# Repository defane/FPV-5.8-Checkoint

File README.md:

# Lëtz Timer

*(technical name: `LetzTimer`; formerly "FPV 5.8 Checkpoint")*

A **"a drone just passed"** platform: a C5 sweeps the 8 Raceband channels and
detects a drone pass on any of them, and a C6 master times it and plays a coin sound, with a
phone-friendly web UI to tune it and watch events. Each gate is a C5 wired to a
C3 (or to the C6); a C3 with no master in reach serves its own web page with the
passes. It scales to a multi-gate race-timing fleet.

> **Derivative and credits.** The detector's receive engine (`components/sdr_rx`) is ported from
> [widscan58](https://github.com/CapnBry/widscan58) by **CapnBry** (commit `a9fff97`: radio, calibration
> cache, PSD/FFT, level metrics, LO planner, linker guard), whose radio layer is derived from
> [esp-sdr](https://github.com/ESPARGOS/esp-sdr) by **ESPARGOS** (commit `a8eaac1`: the PHY I/Q dump
> capture, RX path, gain and analog filter control). Those files keep their GPL-3.0-or-later notices.
> This project started from [C5VRX](https://github.com/Twotoz/C5VRX) — **C5VRX-5, by Twotoz and the C5VRX
> contributors** (upstream `6bc9e4b`) — and is no longer a fork: the C5VRX receive engine was removed (issue #2) and
> the platform around it is new. Some C5VRX material remains and keeps its credit: the C5 PHY I/Q dump format first decoded by C5VRX-1, the console
> structure, the firmware id and NVS helpers, the Raceband scan benches and the off-grid tuning finding
> (zerowidth PR #3). Visit the [official C5VRX website](https://twotoz.github.io/C5VRX/) for the original
> project; its Discord invite is available there. This repository adds the pass detector, the coin
> sound (on the C6 master), and the C5↔C3/C6 platform around it. GPL-3.0-only (see `LICENSE`), without
> any warranty (sections 15–17); the C3 and C6 web pages show this notice in their footer. Not an
> official release of C5VRX, esp-sdr or widscan58, and not endorsed by their authors.

## What it is

- **ESP32-C5** (`firmware/detector`, Waveshare ESP32-C5-Zero) — runs the **sdr_rx**
  engine (`components/sdr_rx`): snapshots of the PHY's I/Q dump at 80 MS/s, one LO for
  two channels (5677/5751/5825/5899 MHz), a 4 × 64-point integer PSD with moment-based
  I/Q correction and the ±5 MHz band power of each channel, ~500 times a second per
  channel (widscan58's measurement; not yet measured on this board). It detects a pass
  on any of R1 to R8 and reports it over a UART link to its bridge. It has no local
  output: no picture, no amplifier and no status LED.
- **ESP32-C3** (`firmware/node`) — a node bridge: UART to the C5, ESP-NOW uplink to
  the C6 master; if no master is reachable at boot it falls back to a local
  Wi-Fi SoftAP + web (results, the C5's health and its
  calibrate/reboot commands).
- **ESP32-C6** (`firmware/master`) — the optional **race-timing master**: UART to its
  own C5, the centralized speaker, a Wi-Fi AP web, and an ESP-NOW hub that
  aggregates the C3 nodes. Each gate is a C5; the C6 times laps per channel,
  shows every gate's health and runs its calibrations and reboots (production
  has no USB console: [docs/fleet.md](docs/fleet.md#gate-health-and-remote-commands-no-console-in-production)).

The web has **two roles**: **spectators** watch the live standings and status
read-only (no login), while **admin** actions — pairing, gate order, reset,
volume, the fleet's re-arm drop, a gate's calibration or reboot, and (on a
degraded C3) detector tuning — require the admin password
(`CONFIG_*_ADMIN_PASSWORD`, no username): the admin toggle in the
header opens a password dialog. The password never crosses the Wi-Fi: the page
signs each admin request (HMAC-SHA256, per-session counter against replays)
with a key derived from it (PBKDF2), the only form the firmware holds (the tab keeps that key, never
the password, in its sessionStorage, so a reload stays admin until the tab closes or you switch admin off). A sniffed
request still allows offline guessing, so choose a long random password
([docs/fleet.md](docs/fleet.md), `components/web_auth`).

## Layout

```
components/
  sdr_rx/        receive engine (C5 only): dump capture, LO pairs, PSD + IQ correction (pure-C parts host-tested)
  letztimer/     the scan task, console and benches, pass detection + the C5<->bridge UART link
  pass_detector/ pure-C pass detector and scan detector (host-tested)
  audio_player/  I2S coin-sound player (the C6 speaker in a fleet)
  link_proto/    pure-C C5<->bridge UART protocol (host-tested)
  fleet_proto/   pure-C C6<->C3 ESP-NOW protocol (host-tested)
  race_timing/   pure-C lap/sector timing engine (host-tested)
  espnow_link/   ESP-NOW transport carrying fleet_proto (C6 + C3)
  status_led/    single-WS2812 status indicator (pure-C core host-tested)
  web_auth/      signed admin requests for the C3/C6 web (pure-C core + auth.js host-tested)
firmware/detector/  ESP32-C5 application (RF + detection, report-only)
firmware/node/      ESP32-C3 node bridge (UART + ESP-NOW relay, degraded Wi-Fi web)
firmware/master/    ESP32-C6 master (UART + ESP-NOW hub + speaker + admin web + timing)
docs/            LETZTIMER.md (index) + detector/no-video-audio/fleet/status-led/bench, wiring-*.svg
```

See **[docs/LETZTIMER.md](docs/LETZTIMER.md)** for the feature notes, the fleet
and the bench procedure, and **[docs/wiring-node.svg](docs/wiring-node.svg)** for
a gate's wiring (C3 + C5).

## Build

The root `Makefile` is the quick path: `make firmware` builds every variant,
`make flash [FW=<name>] [PORT=<port>]` flashes one (interactive firmware/port
menu if an arg is omitted), `make monitor`, `make variants` (list the `FW=`
names: `detector`/`node`/`master` defaults plus variants like
`detector-ipex` (a C5-Zero on its IPEX connector, for an external antenna),
`detector-xiao-c5`, `detector-wave-c5-lcd`, `master-wave-c5`, `master-wave-s3`), `make clean`. flash/monitor fall
back to esptool / a serial terminal on the already-built image when ESP-IDF is
not installed, so you can build in one place and flash in another.

For local, uncommitted settings — the Wi-Fi AP and admin-web passwords, or
enabling audio — put them in `firmware/<role>/sdkconfig.local.defaults` (one
`CONFIG_...=...` per line). It is gitignored, and `make`/`tools/fw.sh` append it
last so it overrides the committed defaults.

To work on the web pages without a board, `make web-master` (<http://127.0.0.1:8080/>)
or `make web-node` (port 8081) runs `tools/web_mock.py`: it serves the real pages from
disk, so a browser reload shows an edit, no build and no flash. `/api/*` answers like
the firmware on a simulated race (now and then a drone lingers at a gate, its channel
framed in cooldown), admin actions take effect (password `letztimer`) and
signed requests are checked as on the ESP. `WEB_ARGS` passes its options: `--vtx` (a
strong carrier on every gate, for the calibration guard; each gate's channel then stays
in cooldown after its first pass), `--latency 300`, `--host
0.0.0.0` (to open it from a phone), `--password ""`. Stopping and restarting it is an
ESP reboot.

The raw commands:

```sh
. ~/esp/esp-idf-v6.0.2/export.sh
( cd firmware/detector && idf.py build )  # esp32c5 → build/detector-c5.bin (0 warnings)
( cd firmware/node && idf.py build )      # esp32c3 → build/node-c3.bin
( cd firmware/master && idf.py build )    # esp32c6 → build/master-c6.bin
# temporary "C5 as master" (run the master firmware on a spare C5 until the C6 arrives) → build-c5/master-c5.bin:
( cd firmware/master && idf.py -DIDF_TARGET=esp32c5 -DSDKCONFIG=sdkconfig.c5 \
    -DSDKCONFIG_DEFAULTS=sdkconfig.c5.defaults -B build-c5 build )

# Host tests
cd test
cc -O2 -std=c11 -Wall -Wextra -Werror -I../components/sdr_rx -I../components/sdr_rx/include test_sdr_dsp.c \
   ../components/sdr_rx/sdr_psd.c ../components/sdr_rx/sdr_level.c -lm -o /tmp/t && /tmp/t
cc -O2 -std=c11 -Wall -Wextra -Werror -I../components/sdr_rx -I../components/sdr_rx/include test_sdr_plan.c \
   ../components/sdr_rx/sdr_plan.c -o /tmp/t && /tmp/t
cc -O2 -std=c11 -Wall -Wextra -Werror -I../components/pass_detector/include \
   test_pass_detector.c ../components/pass_detector/pass_detector.c -lm -o /tmp/t && /tmp/t
cc -O2 -std=c11 -Wall -Wextra -Werror -I../components/pass_detector/include test_scan_detector.c \
   ../components/pass_detector/scan_detector.c ../components/pass_detector/pass_detector.c -lm -o /tmp/t && /tmp/t
cc -O2 -std=c11 -Wall -Wextra -Werror -I../components/pass_detector/include -I../components/sdr_rx \
   -I../components/sdr_rx/include test_pair_ghost.c ../components/pass_detector/scan_detector.c \
   ../components/pass_detector/pass_detector.c ../components/sdr_rx/sdr_psd.c ../components/sdr_rx/sdr_level.c \
   ../components/sdr_rx/sdr_plan.c -lm -o /tmp/t && /tmp/t   # the guard end to end on the DSP
cc -O2 -std=c11 -Wall -Wextra -Werror -I../components/audio_player/include \
   test_audio_resample.c -lm -o /tmp/t && /tmp/t
cc -O2 -std=c11 -Wall -Wextra -Werror -I../components/link_proto/include \
   test_link_proto.c ../components/link_proto/link_proto.c -o /tmp/t && /tmp/t
cc -O2 -std=c11 -Wall -Wextra -Werror -I../components/fleet_proto/include -I../components/link_proto/include \
   test_fleet_proto.c ../components/fleet_proto/fleet_proto.c ../components/link_proto/link_proto.c -o /tmp/t && /tmp/t
cc -O2 -std=c11 -Wall -Wextra -Werror -I../components/race_timing/include \
   test_race_timing.c ../components/race_timing/race_timing.c -o /tmp/t && /tmp/t
cc -O2 -std=c11 -Wall -Wextra -Werror -I../components/status_led/include \
   test_status_led.c ../components/status_led/status_led.c -o /tmp/t && /tmp/t
cc -O2 -std=c11 -Wall -Wextra -Werror -I../components/web_auth/include \
   test_web_auth.c ../components/web_auth/web_auth.c -o /tmp/t && /tmp/t
cc -O2 -std=c11 -Wall -Wextra -Werror -I../components/letztimer \
   test_hop_stats.c -lm -o /tmp/t && /tmp/t
node test_web_auth.mjs   # the page side (auth.js), Node 18+
node test_web_bubble.mjs # the pages' info bubbles: one snippet, mouse, touch and keyboard
python3 test_web_mock.py # tools/web_mock.py against the firmware's /api/state and buffers
python3 test_pcb.py      # hardware/ boards against the firmware's Kconfig pin defaults
python3 test_scan_analyze.py   # tools/scan_analyze.py on synthetic recordings
python3 test_flash_tool.py     # tools/flash.py: download key, --check, logs
```

After editing a `firmware/detector/sdkconfig*.defaults`, run `tools/fw.sh clean`: it
deletes every build dir and generated `sdkconfig`/`sdkconfig.<variant>` (never a
`*.defaults`), since ESP-IDF never reapplies the defaults.

## Architecture

- **Global schema:** at the top of this page ([docs/fleet.svg](docs/fleet.svg)).
- **Pin-level wiring, per set type:**
  - master **C6 + C5**: [docs/wiring-master.svg](docs/wiring-master.svg)
  - node **C3 + C5** (also a gate with no master: the C3 then serves the web): [docs/wiring-node.svg](docs/wiring-node.svg)
  - temporary **C5 + C5** (a spare C5 runs the master firmware until the C6 arrives): [docs/wiring-c5c5.svg](docs/wiring-c5c5.svg)

## Pinout

Each UART link is crossed (one side's TX to the other's RX) with a common
ground. Pins are Kconfig defaults (`menuconfig`). USB-Serial-JTAG (flashing/console)
is reserved on every board. [`hardware/`](hardware/README.md) has carrier PCBs for
both sets, with Gerbers ready to order.

**ESP32-C5** (`firmware/detector`, detector — one per gate)

| Function | GPIO | Notes |
| --- | --- | --- |
| Link UART TX → bridge RX | 6 | to a C3 (node) or the C6 (master) |
| Link UART RX ← bridge TX | 8 | C5-Zero header pin (GPIO 15 is not broken out) |
| Amplifier / status LED | — | none on a detector: the C6 master plays the sound |
| forbidden | 13,14 (USB) · 16-22 (flash) · 26 (antenna) | console, flash, C5-Zero antenna switch |
| free | 0-5, 7, 9-12, 23-25, 27 | the sdr_rx engine uses no GPIO; 2, 7, 25, 27 (and 28, BOOT) are strapping pins: free after boot, no external pull or load that holds them at reset; 27 is the C5-Zero's WS2812 (unused) |

**ESP32-C3** (`firmware/node`, node bridge)

| Function | GPIO | Notes |
| --- | --- | --- |
| UART TX → C5 RX (8) | 5 | |
| UART RX ← C5 TX (6) | 4 | |
| Wi-Fi / ESP-NOW | — | no GPIO; ESP-NOW to the C6 on the shared AP channel |

**ESP32-C6** (`firmware/master`, master)

| Function | GPIO | Notes |
| --- | --- | --- |
| UART TX → local C5 RX (8) | 4 | |
| UART RX ← local C5 TX (6) | 5 | |
| Amplifier BCLK / LRC / DIN / SD | 18 / 19 / 20 / 21 | the centralized speaker; `VIN` 5 V, `OUT±` to a 4 Ω speaker |
| Wi-Fi AP + ESP-NOW | — | admin web + fleet hub; same channel as the nodes |

The C6 AP, the C3 APs and ESP-NOW must share the **same Wi-Fi channel**
(`CONFIG_C6_AP_CHANNEL` / `CONFIG_C3_AP_CHANNEL`).

## Safety

> [!WARNING]
> This is experimental and built on an experimental receive engine. Bugs, signal
> loss or automatic receive-chain changes can cause missed or false passes even
> after an apparently successful test. Do not rely on it as your only means of
> maintaining safe control of an aircraft.

## Attribution

Receive engine (`components/sdr_rx`): **widscan58** by CapnBry —
<https://github.com/CapnBry/widscan58>, commit `a9fff97`. Ported from its
`firmware/src/radio/` (`radio.h`; `c5/radio_c5.c`, `recal_c5.c`, `sram_guard.ld`,
`hot_iram.lf`), `firmware/src/dsp/` (`psd.c`, `fft_r4_sc16.h`, `fft_twiddle_q15.h`) and
`firmware/src/scan/` (`metrics.c`, `planner.c`, the hop of `scanner.c`); the bench
methods of `components/letztimer/lt_bench.c` (tune timing, settle, image rejection,
noise per FFT size) follow its measurement log (`PLAN.md`). Its radio layer is derived
from **esp-sdr** by ESPARGOS — <https://github.com/ESPARGOS/esp-sdr>, commit `a8eaac1`
(`main/families/c5_c6_c61/receiver.c`, `main/targets/esp32c5/`,
`main/common/rx_recalibration.c`, `main/common/burst_gain.h`). The ported files keep
their GPL-3.0-or-later notices and list their changes in their headers.

History: this project started from **C5VRX** by Twotoz and the C5VRX contributors, and is no longer a fork —
<https://github.com/Twotoz/C5VRX> · <https://twotoz.github.io/C5VRX/> (Discord
invite on the website), at upstream `6bc9e4b`. The C5VRX-5 receive engine ran the
detector until issue #2 and is removed (`main` keeps it until a board
bench validates sdr_rx). Still used from C5VRX-5: the console structure and its
download-key reboot (`components/letztimer/lt_console.c`, the reboot of
`components/sdr_rx/sdr_radio_c5.c`), the firmware id and NVS helpers
(`components/letztimer/fw_id.c`, `lt_nvs.c`), `tools/flash.py` and
`tools/enter_download.py`, and the off-grid tuning finding of zerowidth/C5VRX PR #3.
The Raceband scan benches first built on the C5VRX engine (issue #1) give
`lt_bench.c` the shape of its scan recording and residue trace. Reused material keeps
its original copyright, license and credits; see `AGENTS.md` for the reuse policy and
`assets/BRANDING.md` for branding terms.

Research provenance: the PHY I/Q dump engine was first decoded in C5VRX-1 (librftest
`adctrig`, registers `0x600a9004/08/18`, bank `0x40830000`, 10-bit I/Q words: upstream
`legacy/c5vrx1/research/adc-dump-format.md`), and C5VRX-3/5 drove it continuously
(`enable_continuous_modem`, upstream `main/rf.c:119-147`). sdr_rx takes a different
route: one-shot snapshots, as esp-sdr and widscan58 trigger them. Source: raw source 15,
after the PHY's ADC-rate/RX-filter stage. Rate: 80 MS/s. Size: 256 words per capture
(3.2 µs). Ownership: CPU-polled, no DMA, no ring, no DAC. Word format: I bits 0–9,
Q bits 10–19, signed.

For the history, C5VRX-5 builds on C5VRX-2..4 (the continuous MODEM_DIAG to
BitScrambler video path, Direct Gain V3-V5, the PAIR schedule and the U85Q study of
PR #190), on zerowidth/C5VRX PR #3 (interference-burst gate, sampling-phase probe,
off-grid channel tuning), on Louis Hitchcock's staged overload recovery (C5VRX
#182/#184), and on ESPARGOS esp-sdr (GPL-3.0) for the C5 RX filter control. Espressif
supplied the GDMA EOF fix (espressif/esp-idf#19091).

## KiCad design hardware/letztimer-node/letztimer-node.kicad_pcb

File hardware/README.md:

# Carrier boards

Two 2-layer boards that hold the modules of a set, every USB-C on the same edge, with solder
pads for the power.

| Board | Modules | Size | To order |
| --- | --- | --- | --- |
| node | C5-Zero + C3-Zero | 57 × 24 mm | [`gerbers/letztimer-node-gerbers.zip`](gerbers/letztimer-node-gerbers.zip) |
| master | C5-Zero + C6-Zero + MAX98357A | 79 × 24 mm | [`gerbers/letztimer-master-gerbers.zip`](gerbers/letztimer-master-gerbers.zip) |

**No board has been built yet.** The design rules pass, the drill data matches Waveshare's
drawings and `test/test_pcb.py` ties the nets to the firmware, but nothing has been soldered
or powered. Order a small batch first.

## Before ordering

Print `letztimer-*/letztimer-*-1to1.pdf` at 100 % and lay the real modules on the paper.
Check the MAX98357A closely: the footprint comes from Adafruit's board. Other breakouts
usually share its 7-pin order, but compare yours with the `LRC`…`VIN` labels on the board.

## Ordering

Upload the zip as it is. It holds both copper layers, solder mask, silkscreen, the outline
and the drill files.

2 layers, FR-4, 1.6 mm, 1 oz copper, any finish. No stencil or assembly needed.

## Parts

[`BOM.csv`](BOM.csv) lists each board's parts with an order reference. `test/test_pcb.py` checks
it against the node and master boards.

The `-M` Waveshare modules cost a little more but come with their headers fitted, which saves
the 1×9 headers and 18 joints per module. SS34 diodes must be in the **SMA** package.

## Assembly

1. Solder R1, R2, D1 and D2. The bar on a diode faces the module.
2. Before fitting a module, check J1 and J2 are not shorted, feed 5 V and read a little under
   5 V on the `5V` holes of U1 and U2.
3. Fit the modules on their headers, components up, **USB towards the top edge**. U1 hangs
   4 mm past the bottom edge, on purpose.
4. Master: fit the amplifier components up, its pin row on the `U3` labels. The speaker goes
   to the breakout's own terminal.

Then flash as usual, with `make flash FW=detector` for U1 and `FW=node` or `FW=master` for U2.

## Power

Feed the pads with **4.6 to 5.5 V**: 1 A for a node, 2 A for a master.

The `5V` pin of the C5-Zero and C3-Zero **is** the USB VBUS, with no diode (the C6-Zero has
its own B5819WS). Wired directly, a supply on the pads would feed the PC's USB port and two
cables would tie two hosts together. So each side gets its own diode, and USB can stay
plugged in while the pads are powered, which is the normal way to debug a running gate:

| Plugged in | C5 | C3 / C6 | Amplifier |
| --- | --- | --- | --- |
| Pads | on | on | on |
| USB on the C5 | on | off | off |
| USB on the C3 | off | on | — |
| USB on the C6 | off | on | on |
| Pads and any USB | on | on | on |

The diodes also protect the whole board if the power wires are swapped. They drop about 0.4 V,
which every regulator here tolerates. The 5.5 V limit is that of the C5-Zero's converter and
of the amplifier, kept on the pads as a margin.

R1 and R2 exist because of those diodes: a module can now be running while the other one is
off, and they hold the current into the sleeping chip's pin to about 3 mA. At 115200 baud
they change nothing.

## Layout notes

- **USB:** each module's end is flush with the top edge, so its USB-C sticks out by about
  1.6 mm and two plugs fit side by side. BOOT and RESET stay reachable on top.
- **Antennas:** the board stops short of the C5's ceramic antenna and IPEX connector, and a
  12 mm notch leaves no copper or FR-4 under any antenna.
- **Receiver pins:** the C5's GPIO 0 to 5 stay unconnected (they carried C5VRX's IQ
  loopback; the sdr_rx engine uses no GPIO), like every C5 pin but `5V`, `GND` and the link
  (GPIO 6 and 8). Those two are not strapping pins.
- **C6 strapping pins:** the link uses GPIO 4 and 5, which only set the SDIO clock edges and do
  not affect a boot from flash. GPIO 8, 9 and 15 are left unconnected.
- **Speaker terminal:** its pins may poke through the breakout, so the master has no copper
  under them.

## Still to check on a real board

- **Detection:** the C5's antenna now sits about 2 cm from the C3's or C6's 2.4 GHz antenna.
  Compare the `levels` and false passes with the wired setup, with Wi-Fi active.
- **Heat** in D2 on a master at full volume.
- **Temporary C5-as-master set:** not supported, its amplifier pins differ.

## Antenna

[`antenna/`](antenna/README.md) holds a directive 5.8 GHz quasi-Yagi on FR-4, a separate board
that reaches a C5-Zero through its IPEX connector. Its openEMS model gives about 4.5 dBi along its
axis across the Raceband, in a beam 64° by 84° wide. It has not been built.

## Enclosure

[`enclosure/`](enclosure/README.md) holds a 3D-printed box for a node or a master set, with its
LiPo cut-off and DC-DC converter (and the master's speaker), and an arm that points the antenna
in 8 directions and rolls it about its own axis in 8 steps. Its source is a SolidCraft design
with one configuration per set. It has not been printed yet.

## Regenerating

[`generate_boards.py`](generate_boards.py) is the source of the boards: edit it, not the KiCad
files, which it overwrites. It needs KiCad 9 (`pcbnew` and `kicad-cli`):

```sh
python3 hardware/generate_boards.py   # writes the boards, fills, runs the DRC, exports
python3 test/test_pcb.py              # no KiCad needed; run in CI
```

The DRC result is printed for each board and must read `violations [] unconnected 0`.

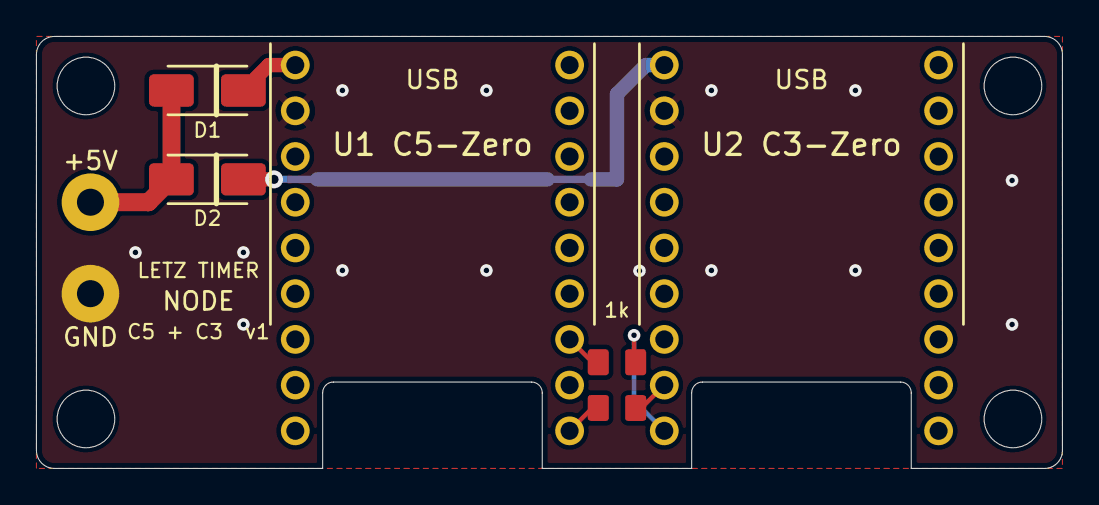
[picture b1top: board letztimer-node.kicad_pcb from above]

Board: 2 copper layers, 57.0 x 24.0 mm, 12 parts (0 on the bottom side), 8 nets.

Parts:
D1, D2: SS34 3A 40V SMA; SS34
H1, H2, H3, H4: M3 hole; M3
J1: +5V wire pad; +5V
J2: GND wire pad; GND
R1, R2: 1k 0805; 1k
U1: C5-Zero
U2: C3-Zero

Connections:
5V_BRIDGE: D2.1, U2.5V
5V_C5: D1.1, U1.5V
+5V: D1.2, D2.2, J1.1
BRIDGE_RX: R1.2, U2.4
BRIDGE_TX: R2.2, U2.5
C5_RX: R2.1, U1.8
C5_TX: R1.1, U1.6
GND: J2.1, U1.GND, U2.GND
